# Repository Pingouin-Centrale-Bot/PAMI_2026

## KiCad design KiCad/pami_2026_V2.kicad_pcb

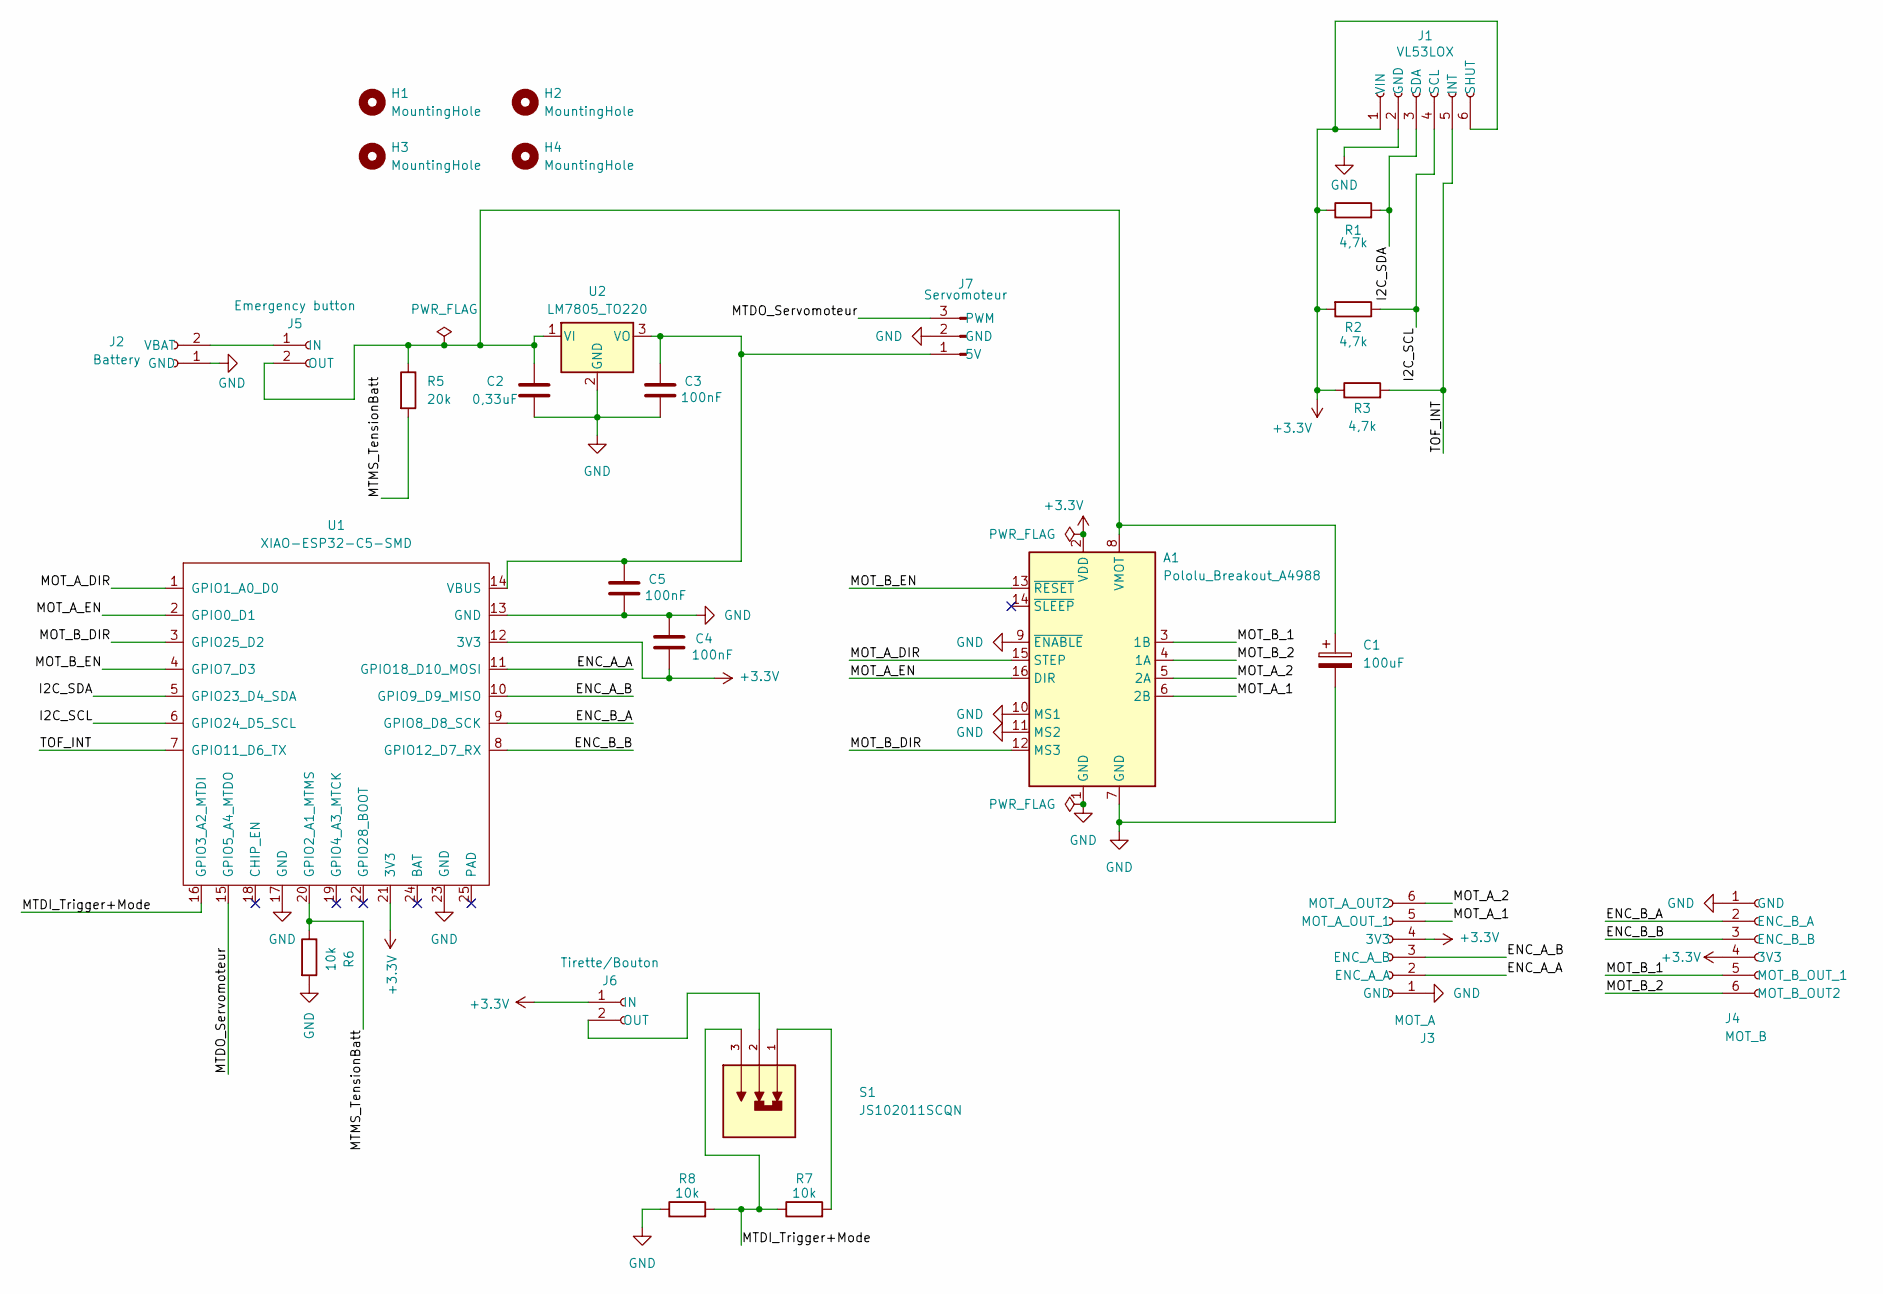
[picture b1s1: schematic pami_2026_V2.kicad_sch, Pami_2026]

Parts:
A1: Pololu_Breakout_A4988; Pololu_Breakout-16_15.2x20.3mm
C1: 100uF; CP_Elec_6.3x7.7
C2: 0,33uF; C_0805_2012Metric
C3, C4, C5: 100nF; C_0805_2012Metric
H1, H2, H3, H4: MountingHole; MountingHole_3.2mm_M3
J1: VL53LOX; PinHeader_1x06_P2.54mm_Vertical
J2: Battery; JST_XH_B2B-XH-A_1x02_P2.50mm_Vertical
J3: MOT_A; JST_PH_B6B-PH-K_1x06_P2.00mm_Vertical
J4: MOT_B; JST_PH_B6B-PH-K_1x06_P2.00mm_Vertical
J5: Emergency button; JST_XH_B2B-XH-A_1x02_P2.50mm_Vertical
J6: Tirette/Bouton; JST_XH_B2B-XH-A_1x02_P2.50mm_Vertical
J7: Servomoteur; PinHeader_1x03_P2.54mm_Vertical
R1, R2, R3: 4,7k; R_0805_2012Metric
R5: 20k; R_0805_2012Metric
R6, R7, R8: 10k; R_0805_2012Metric
S1: JS102011SCQN; SW_JS102011SCQN; PARTREV 8 Oct 21
U1: XIAO-ESP32-C5-SMD
U2: LM7805_TO220; TO-220-3_Vertical

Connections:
+3.3V: A1.2 (VDD), C4.2, J1.1 (VIN), J1.6 (SHUT), J3.4 (3V3), J4.4 (3V3), J6.1 (IN), R1.1, R2.2, R3.1, U1.12 (3V3), U1.21 (3V3)
/ENC_A_A: J3.2 (ENC_A_A), U1.11 (GPIO18_D10_MOSI)
/ENC_A_B: J3.3 (ENC_A_B), U1.10 (GPIO9_D9_MISO)
/ENC_B_A: J4.2 (ENC_B_A), U1.9 (GPIO8_D8_SCK)
/ENC_B_B: J4.3 (ENC_B_B), U1.8 (GPIO12_D7_RX)
/I2C_SCL: J1.4 (SCL), R2.1, U1.6 (GPIO24_D5_SCL)
/I2C_SDA: J1.3 (SDA), R1.2, U1.5 (GPIO23_D4_SDA)
/MOT_A_1: A1.6 (2B), J3.5 (MOT_A_OUT_1)
/MOT_A_2: A1.5 (2A), J3.6 (MOT_A_OUT2)
/MOT_A_DIR: A1.15 (STEP), U1.1 (GPIO1_A0_D0)
/MOT_A_EN: A1.16 (DIR), U1.2 (GPIO0_D1)
/MOT_B_1: A1.3 (1B), J4.5 (MOT_B_OUT_1)
/MOT_B_2: A1.4 (1A), J4.6 (MOT_B_OUT2)
/MOT_B_DIR: A1.12 (MS3), U1.3 (GPIO25_D2)
/MOT_B_EN: A1.13 (~RESET), U1.4 (GPIO7_D3)
/MTDI_Trigger+Mode: R7.1, R8.2, S1.3, U1.16 (GPIO3_A2_MTDI)
/MTDO_Servomoteur: J7.3 (PWM), U1.15 (GPIO5_A4_MTDO)
/MTMS_TensionBatt: R5.2, R6.1, U1.20 (GPIO2_A1_MTMS)
/TOF_INT: J1.5 (INT), R3.2, U1.7 (GPIO11_D6_TX)
GND: A1.1 (GND), A1.7 (GND), A1.9 (~ENABLE), A1.10 (MS1), A1.11 (MS2), C1.2, C2.2, C3.2, C4.1, C5.2, J1.2 (GND), J2.1 (GND), J3.1 (GND), J4.1 (GND), J7.2 (GND), R6.2, R8.1, U1.13 (GND), U1.17 (GND), U1.23 (GND), U2.2 (GND)
unnamed: A1.8 (VMOT), C1.1, C2.1, J5.2 (OUT), R5.1, U2.1 (VI)
unnamed: J2.2 (VBAT), J5.1 (IN)
unnamed: J6.2 (OUT), S1.2
unnamed: C3.1, C5.1, J7.1 (5V), U1.14 (VBUS), U2.3 (VO)
unnamed: R7.2, S1.1

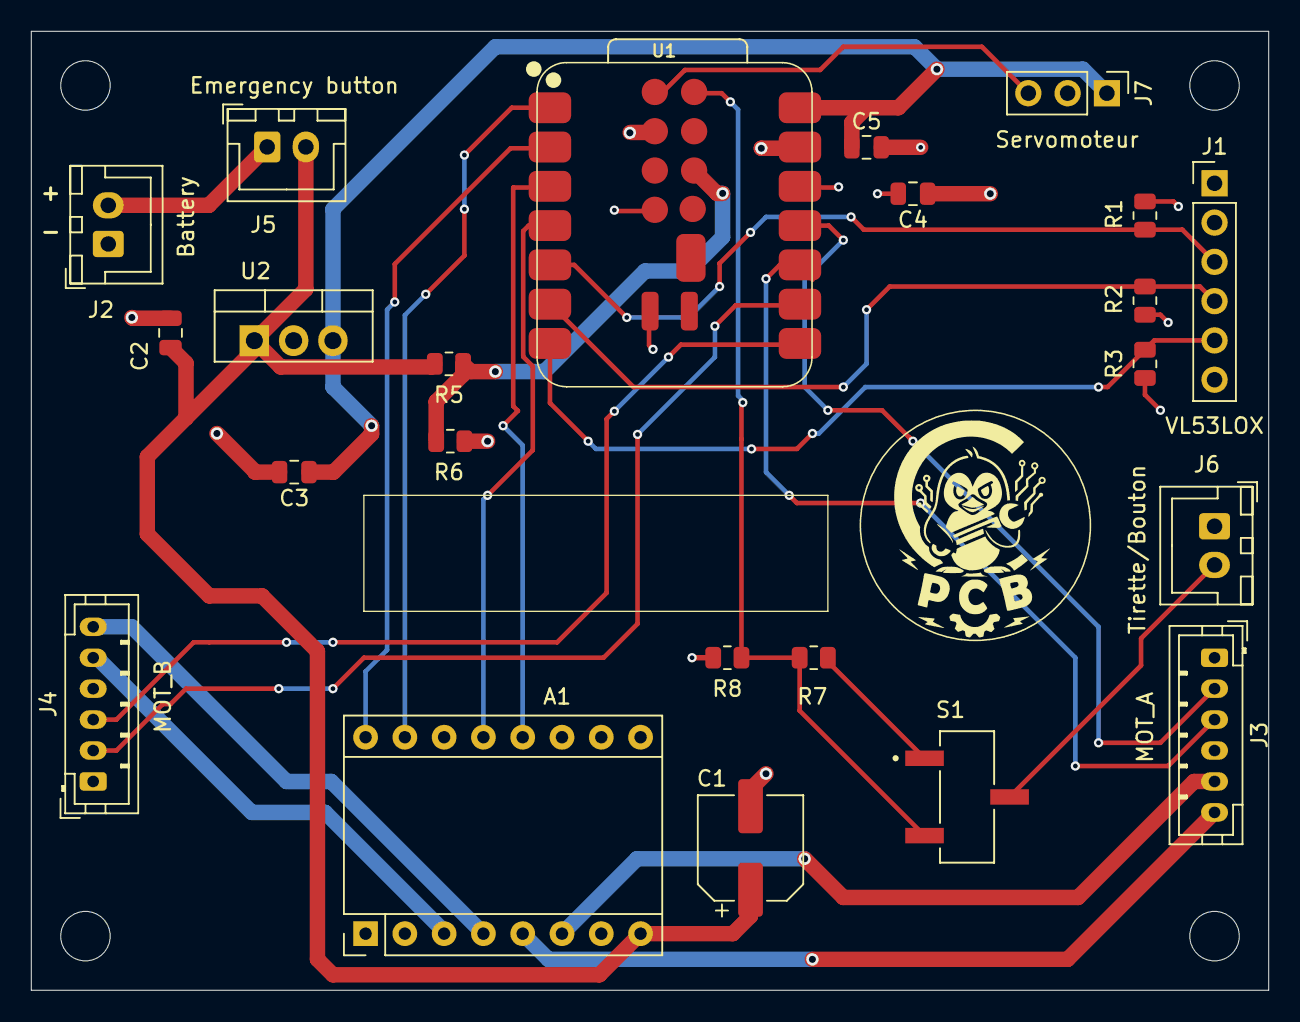
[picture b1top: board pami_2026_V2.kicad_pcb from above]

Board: 4 copper layers, 80.0 x 62.0 mm, 27 parts (0 on the bottom side), 25 nets.

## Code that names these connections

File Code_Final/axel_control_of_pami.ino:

#include <Wire.h>
#include <Adafruit_VL53L0X.h>
#include <ESP32Servo.h>

// PINS

#define DIR_A 0
#define PWM_A 1

#define DIR_B 7
#define PWM_B 25

#define ENC_A_A 10
#define ENC_A_B 9

#define ENC_B_A 8
#define ENC_B_B 12

#define SDA_PIN 23
#define SCL_PIN 24

#define SERVO_PIN 3
#define TIRETTE_PIN 5

// ===================== OBSTACLE =====================
const int distanceObstacleMM = 120;
const unsigned long tempsClearObstacleMS = 2000;

// ===================== CONSTANTE SELECTION MODE ET TIRETTE =====================
const float SEUIL_TIRETTE_V = 0.50f; // 0V (tirette retirée) < 0.5 < 1.65V (tirette en place) 
const float SEUIL_MODE_V    = 2.50f;
const int JAUNE = 1;
const int BLEU = -1;
int MODE = 0;

// ===================== ROBOT =====================
const float diametreRoueMM = 38.0;
const float tickParTour = 2340.0;
const float mmParTick = (diametreRoueMM * PI) / tickParTour;
const float TICKS_PAR_MM = tickParTour / (diametreRoueMM * PI);  // ≈ 18,6  ticks/mm

const float ENTRE_ROUES_MM = 120.0 ;

// ===================== PWM =====================
const int pwmFrequence = 20000;
const int pwmResolution = 8;


// ===================== SELECTEUR MODE ET TIRETTE =====================
// Interrupteur position HAUTE (COTE S1) pour BLEU (1.65V), BASSE (VERS L'ARRIERE DU PAMI) pour JAUNE (3.3V)

float lireTension_tirette() {
  // Moyenne sur 8 lectures pour stabiliser 
  long sum = 0;
  for (int i = 0; i < 8; i++) { sum += analogRead(TIRETTE_PIN); delay(1); }
  return (sum / 8.0f) * 3.3f / 4095.0f;
}

int select_mode() {
  float v = lireTension_tirette();
  int mode = (v > SEUIL_MODE_V) ? JAUNE : BLEU;
  Serial.println(mode == JAUNE ? "JAUNE" : "BLEU");
  return mode;
  }

void attendreTirette() {
  //Lire le mode pendant que la tirette est en place
  MODE = select_mode();

  // Attendre que la tirette soit retirée (tension < seuil)
  while   (lireTension_tirette() >= SEUIL_TIRETTE_V) {
    stopMotors();
    delay(20);
  }
  }

void attendre_remet_Tirette() {
  while (lireTension_tirette() < SEUIL_TIRETTE_V) {
    delay(100);
  }
  }

// ===================== TOF =====================
Adafruit_VL53L0X lox;
uint16_t lireDistanceMM() {
  VL53L0X_RangingMeasurementData_t measure;
  lox.rangingTest(&measure, false);

  if (measure.RangeStatus != 4) {
    return measure.RangeMilliMeter;
  }

  return 0;
}

bool obstacleDetecte() {
  uint16_t d = lireDistanceMM();

  if (d > 0 && d < distanceObstacleMM) {
    Serial.print("Obstacle : ");
    Serial.print(d);
    Serial.println(" mm");
    return true;
  }

  return false;
}

void attendreObstacleDisparu() {
  stopMotors();

  unsigned long debutSansObstacle = 0;

  while (true) {
    bool obstacle = obstacleDetecte();

    if (!obstacle) {
      if (debutSansObstacle == 0) {
        debutSansObstacle = millis();
      }

      if (millis() - debutSansObstacle >= tempsClearObstacleMS) {
        return;
      }
    } else {
      debutSansObstacle = 0;
    }

    delay(50);
  }
}

// SERVO

Servo monServo;
void actionServoFin() {
  monServo.write(0);
  delay(300);

  monServo.write(90);
  delay(700);

  monServo.write(0);
  delay(300);
}

// MOTORS

volatile long ticksGauche = 0;
volatile long ticksDroit = 0;

volatile uint8_t prevStateL = 0;
volatile uint8_t prevStateR = 0;

const int8_t qTable[16] = {
  0, -1, +1, 0,
  +1, 0, 0, -1,
  -1, 0, 0, +1,
  0, +1, -1, 0
};


// ISR
void IRAM_ATTR isrLeft() {
  uint8_t a = digitalRead(ENC_A_A);
  uint8_t b = digitalRead(ENC_A_B);

  uint8_t state = (a << 1) | b;
  uint8_t index = (prevStateL << 2) | state;

  ticksGauche += qTable[index];
  prevStateL = state;
}

void IRAM_ATTR isrRight() {
  uint8_t a = digitalRead(ENC_B_A);
  uint8_t b = digitalRead(ENC_B_B);

  uint8_t state = (a << 1) | b;
  uint8_t index = (prevStateR << 2) | state;

  ticksDroit -= qTable[index];
  prevStateR = state;
}

void setMotor(int dirPin, int pwmPin, int speedVal) {
  speedVal = constrain(speedVal, -255, 255);

  if (speedVal == 0) {
    ledcWrite(pwmPin, 0);
    return;
  }

  if (speedVal > 0) {
    digitalWrite(dirPin, HIGH);
    ledcWrite(pwmPin, speedVal);
  } else {
    digitalWrite(dirPin, LOW);
    ledcWrite(pwmPin, -speedVal);
  }
}

void setMotors(int gauche, int droit) {
  setMotor(DIR_A, PWM_A, gauche);
  setMotor(DIR_B, PWM_B, droit);
}

void stopMotors() {
  setMotors(0, 0);
}


// Position control

const float Kp = 0.1;
const float Ki = 0.01;
const int DT = 1; // ms


const float error_acceptance = 200.0;

void control_loop(long r_left, long r_right, bool front){
  float error_right = r_right - ticksDroit;
  float error_left = r_left - ticksGauche;

  float integral_error_right = DT*error_right/1000;
  float integral_error_left = DT*error_left/1000;

  unsigned long previous = 0;

  while (abs(error_left) > error_acceptance || abs(error_right) > error_acceptance){
    if (millis() - previous >= DT){
      previous = millis();

      float u_right = -Kp*error_right - Ki*integral_error_right;
      u_right = constrain(u_right, -255, 255);

      float u_left = -Kp*error_left - Ki*integral_error_left;
      u_left = constrain(u_left, -253, 253);

      error_right = r_right - ticksDroit;
      error_left = r_left - ticksGauche;

      integral_error_right = DT*error_right/1000;
      integral_error_left = DT*error_left/1000;

      setMotor(DIR_B, PWM_B, u_left);
      setMotor(DIR_A, PWM_A, u_right);


      Serial.println("-----------------");
      Serial.println(u_left);
      Serial.println(u_right);
      Serial.println(error_left);
      Serial.println(error_right);
    }
  }
  stopMotors();
}

void angular_move_control_loop(float angle){
  int r_left = (100)*10*angle + ticksGauche;
  int r_right = (100 + ENTRE_ROUES_MM)*10*angle + ticksDroit;
  control_loop(r_left, r_right, false);
}

void angular_control_loop(float angle){
  int r_left = -(98)*7*angle + ticksGauche;
  int r_right = +(98)*7*angle + ticksDroit;
  control_loop(r_left, r_right, false);

}

void linear_control_loop(float distance){
  // 92.0 mm -> 10cm
  // distance -> ?
  int r_left = distance * 1000 / 920 + ticksGauche;
  int r_right = distance * 1000 / 920 + ticksDroit;
  control_loop(r_left, r_right, true);
}

// ===================== SETUP =====================

void setup() {

  Serial.begin(115200);
  delay(1000);
  monServo.attach(SERVO_PIN);

  pinMode(DIR_A, OUTPUT);
  pinMode(DIR_B, OUTPUT);

  pinMode(ENC_A_A, INPUT_PULLUP);
  pinMode(ENC_A_B, INPUT_PULLUP);

  pinMode(ENC_B_A, INPUT_PULLUP);
  pinMode(ENC_B_B, INPUT_PULLUP);

  pinMode(TIRETTE_PIN, INPUT_PULLUP);


  ledcAttach(PWM_A, pwmFrequence, pwmResolution);
  ledcAttach(PWM_B, pwmFrequence, pwmResolution);

  stopMotors();

  Wire.begin(SDA_PIN, SCL_PIN);

  if (!lox.begin()) {
    Serial.println("Erreur TOF");
    while (1)
      ;
  }

  monServo.attach(SERVO_PIN);
  monServo.write(0);

  prevStateL = (digitalRead(ENC_A_A) << 1) | digitalRead(ENC_A_B);
  prevStateR = (digitalRead(ENC_B_A) << 1) | digitalRead(ENC_B_B);

  attachInterrupt(digitalPinToInterrupt(ENC_A_A), isrLeft, CHANGE);
  attachInterrupt(digitalPinToInterrupt(ENC_A_B), isrLeft, CHANGE);

  attachInterrupt(digitalPinToInterrupt(ENC_B_A), isrRight, CHANGE);
  attachInterrupt(digitalPinToInterrupt(ENC_B_B), isrRight, CHANGE);
}


void loop() {
  attendreTirette();
  Serial.println(MODE);


  if (MODE == 1){
    // JAUNE
    linear_control_loop(6000);
    angular_control_loop(-PI/3);
    linear_control_loop(10150);
    angular_control_loop(PI/3);
    linear_control_loop(2000);
  }
  else{
    // BLEU
    linear_control_loop(7000);
    angular_control_loop(5*PI/12);
    linear_control_loop(9500);
    angular_control_loop(-5*PI/12);
    linear_control_loop(3000);
  }


  actionServoFin();

  Serial.println("ok");
  attendre_remet_Tirette(); 
}

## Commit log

2025-12-05 Création d'une première version des prototypes (.hpp) commentée, création d'une 1ère version de : DriverInterface.cpp, Encoder.cpp, Motor.cpp (code non testé sur l'esp32)
2026-04-20 Add files via upload
    This file contains :
    - The libraries for the specific components used in the PCB
    - The schematic, pcb and project files
    - The file to import the contraints specified by ailser to manufacture the PCB
2026-04-20 Mise en forme du repo
2026-05-13 Create Code
2026-05-14 retirer les f
2026-05-14 Rename code.ino to axel_control_of_pami.ino
2026-05-15 Code pour match (NON TESTER)
